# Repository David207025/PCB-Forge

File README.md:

# PCB Forge ⚡

A comprehensive, developer-centric documentation toolchain for hardware and PCB engineers. **PCB Forge** integrates a **VS Code extension**, a **native Rust backend (`pcbfapi`)**, automated **KiCad CLI** exports, and an in-memory **Typst** compilation engine to generate publication-grade PDF documentation, manufacturing packets, and schematic sheets directly from your EDA project files.

**Note:** The current repository status is for the new implementation of PCB-Forge. Past versions have been deleted due to incompatibility and performance issues.

---

## 🏗️ Architecture Overview

The PCB Forge monorepo is structured into three primary components:

```
PCB-Forge/
├── pcbfapi/                   # Native Rust background daemon & HTTP server
│   ├── src/
│   │   ├── main.rs            # Axum HTTP server (port 47210), CLI subcommands & system tray
│   │   ├── access.rs          # KiCad detection, TCC permission checking & access requests
│   │   ├── service.rs         # Background daemon manager (launchd, systemd, Windows service)
│   │   ├── forge.rs           # KiCad CLI runner, asset caching & Typst compiler
│   │   ├── definitions.rs     # Typst World implementation & project schema models
│   │   └── tray.rs            # Native macOS / Windows system tray icon & menu
│   └── typst/                 # Vendored Typst packages (e.g., cmarker plugin)
│
├── extension/                 # VS Code extension (TypeScript)
│   ├── src/extension.ts       # Extension entry point, daemon connector & webview provider
│   ├── web-ui/                # Modern React + Vite frontend for template & project editing
│   └── package.json           # Extension manifest & configuration
│
├── docs/                      # Auto-generated Markdown documentation (pcbfapi.md, scripts.md)
└── scripts                    # Workspace build, release, and packaging utilities
```

### How It Works
1. **The API Daemon (`pcbfapi`)**: A secure, persistent background daemon process written in Rust. It runs independently of VS Code, auto-starts on boot (via macOS LaunchAgent, Linux systemd, or Windows startup), and exposes local loopback endpoints on `http://127.0.0.1:47210`.
2. **KiCad Access & Permissions (`pcbfapi/src/access.rs`)**: Automatically checks for `kicad-cli`, resolves permissions, isolates configuration to prevent macOS TCC sandboxing issues, and prompts the user with native OS dialogs if access to KiCad application files is required.
3. **The Extension (`extension/`)**: Seamlessly connects to the background daemon over the HTTP endpoint. Shows daemon connection status in the VS Code status bar and provides commands to manage the service and verify permissions.
4. **Asset Generation & Typst Compilation**: Hardware schematics, layer SVGs, markdown notes, and project metadata are exported via KiCad CLI and compiled in-memory to publication-grade vector PDFs.

---

## ⚙️ Service & Daemon Management

The `pcbfapi` binary can be installed and managed as a background service:

```bash
# Verify KiCad installation and prompt for access if permissions are missing:
pcbfapi check-access

# Service management (auto-starts from boot):
pcbfapi service install    # Register background daemon (macOS LaunchAgent / systemd)
pcbfapi service start      # Start daemon service
pcbfapi service stop       # Stop daemon service
pcbfapi service status     # Inspect daemon & service status
pcbfapi service uninstall  # Remove background service registration
```

### Homebrew Installation & Services
When installing via Homebrew, `pcbfapi` is automatically configured as a background service:
```bash
brew tap David207025/homebrew-pcb-forge
brew install pcbfapi
brew services start pcbfapi
```

---

## 🛠️ Subscripts Tutorial & Reference

The project includes several automation scripts at the repository root. Below is a detailed guide on what each script does and when to use it:

### 1. `deploy-extension.js` — Local Extension Development
* **Command:** `pnpm deploy` or `node deploy-extension.js`
* **What it does:**
  1. Runs `pnpm build` (which compiles `extension/web-ui` with Vite and compiles extension TypeScript with `tsc`).
  2. Runs `node package-extension.js` to create the `.vsix` installer package.
  3. Automatically executes `code --install-extension <path-to-vsix> --force` to install the newly built extension directly into your local VS Code.
* **When to use:** Whenever you make changes to the VS Code extension or webview and want to test them immediately in VS Code.

### 2. `package-extension.js` — VSIX Package Bundler
* **Command:** `pnpm package` or `node package-extension.js`
* **What it does:**
  1. Copies the built webview bundle from `extension/web-ui/dist/` into `extension/web/`.
  2. Invokes `@vscode/vsce package` with clean exclusions (ignoring node_modules, source TS files, and web-ui source code) to produce a lean `.vsix` file in the `build/` directory.
* **When to use:** When you need a clean `.vsix` bundle for distribution without installing it locally.

### 3. `update-version.js` — Monorepo Version Synchronizer
* **Command:** `node update-version.js <new-version>` (e.g. `node update-version.js 0.4.0`)
* **What it does:**
  * Synchronizes the semantic version across all four project manifests in one pass:
    - Root `package.json`
    - Rust crate `pcbfapi/Cargo.toml` (`[package]` section)
    - Extension manifest `extension/package.json`
    - Frontend manifest `extension/web-ui/package.json`
* **When to use:** Before making a new release or when bumping version numbers.

### 4. `generate-docs.js` — Automated Markdown Documentation Generator
* **Command:** `pnpm docs` or `node generate-docs.js`
* **What it does:**
  1. Scans all Rust source files in `pcbfapi/src/` (`main.rs`, `forge.rs`, `definitions.rs`, `tray.rs`), extracting module-level documentation (`//!`) and item doc comments (`///`).
  2. Scans TypeScript and JavaScript scripts for JSDoc comment blocks (`/** ... */`).
  3. Writes comprehensive Markdown documentation files into the `docs/` folder:
     - `docs/pcbfapi.md`: Rust API handlers, endpoints, structs, and compiler world methods.
     - `docs/scripts.md`: Script functions and packaging documentation.
     - `docs/README.md`: Technical documentation index.
* **When to use:** Whenever you add or modify Rust functions, API endpoints, or scripts, or automatically as part of the release workflow.

### 5. `release.sh` — Unified End-to-End Release Pipeline
* **Command:** `./release.sh [new-version]` (e.g. `./release.sh 0.4.0` or `./release.sh`)
* **What it does:**
  1. Updates the version across all manifests if a version parameter is passed.
  2. Runs `node generate-docs.js` to update documentation in `docs/`.
  3. Builds frontend webview and compiles extension TypeScript (`pnpm run build`).
  4. Packages the `.vsix` extension bundle.
  5. Publishes the extension to the VS Code Marketplace if `VSCE_PAT` is defined.
  6. Commits modified files and pushes to `origin main`.
  7. Cleans up any existing GitHub release/tag for this version (using `gh release delete`).
  8. Creates and pushes a fresh Git tag (`vX.Y.Z`), triggering the GitHub Actions `cargo-dist` workflow to build cross-platform binaries, installers, and update the Homebrew tap.
* **When to use:** When you are ready to publish a new official release of PCB Forge.

### 6. `retag.sh` — CI Re-trigger & VSIX Publish Utility
* **Command:** `./retag.sh`
* **What it does:**
  * Reads the current version from `pcbfapi/Cargo.toml`.
  * Builds and packages the `.vsix` bundle and publishes it to the VS Code Marketplace via `@vscode/vsce`.
  * Deletes any existing GitHub Release and local/remote Git tag for that version, then recreates and pushes the tag to re-trigger CI.
* **When to use:** When you need to publish an updated VSIX and re-trigger CI builds for the current version without bumping the version number.

### 7. `wipe-tag.sh` — Tag Teardown Utility
* **Command:** `./wipe-tag.sh`
* **What it does:**
  * Extracts the current version from `pcbfapi/Cargo.toml` and permanently deletes the tag locally and on GitHub remote without recreating it.
* **When to use:** When canceling a release or removing an accidental tag.

### 8. `install-api.sh` — Local CLI Daemon Installation
* **Command:** `./install-api.sh`
* **What it does:**
  * Runs `cargo build --release` inside `pcbfapi/` and copies the compiled binary to `~/.pcb-forge/bin/pcbfapi`.
* **When to use:** When developing or testing the Rust daemon natively on your system.

### 9. `generate_icons.py` — Icon Generator
* **Command:** `python3 generate_icons.py`
* **What it does:**
  * Uses Pillow / Python to generate multi-resolution PNG and icon assets from the master icon files for the system tray and extension.

---

## 🚀 Quick Start for Development

### Prerequisites
- **Node.js** (v18+) & **pnpm**
- **Rust** & **Cargo** (latest stable)
- **KiCad 7+ or 8+** (with `kicad-cli` on PATH)
- **GitHub CLI (`gh`)** (optional, for release management)

### Local Build & Test Loop

1. **Install Dependencies:**
   ```bash
   pnpm install
   ```

2. **Check & Build Rust API Backend:**
   ```bash
   cargo check --manifest-path pcbfapi/Cargo.toml
   cargo build --manifest-path pcbfapi/Cargo.toml
   ```

3. **Develop the VS Code Extension & Webview:**
   ```bash
   # Build frontend and install extension into VS Code:
   pnpm deploy
   ```

4. **Generate Documentation:**
   ```bash
   pnpm docs
   ```

---

## 🧪 Example & Testing Environment

A complete, self-contained example workspace is available in the [`test/`](./test) directory (see [`test/README.md`](./test/README.md) for full setup and usage instructions). It includes a sample `.pcbf` project configuration, cloned **Venturi** KiCad schematic and PCB files, and an automated script that installs the required template into `~/.pcb-forge/templates`, syncs its schema, and compiles a full multi-page PDF document via the `pcbfapi` daemon.

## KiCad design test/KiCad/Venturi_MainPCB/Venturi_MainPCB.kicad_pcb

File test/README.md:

# PCB Forge — Example & Test Workspace

This directory contains a complete, ready-to-run example project (featuring a clone of the **Venturi** PCB hardware files) so you can test **PCB Forge** out of the box.

## Prerequisites

Before running this example, ensure the following are installed on your system:

1. **PCB Forge Daemon (`pcbfapi`)**: Must be installed and running on `127.0.0.1:47210`. See the [root README.md](../README.md) for Homebrew and binary installation instructions.
2. **KiCad (7.0, 8.0, or 9.0)**: `kicad-cli` must be installed and accessible (`pcbfapi check-access`).
3. **VS Code Extension** *(optional, for interactive editing)*: Install the **PCB Forge** extension in VS Code to edit `.pcbf` files with syntax highlighting, inline file pickers, and one-click PDF generation.

## What's Included

- **Sample `.pcbf` Project**: Pre-configured project definition linking schematic, PCB layout, and documentation pages using relative paths.
- **Venturi Hardware Assets**: Reference `.kicad_pcb` and `.kicad_sch` files used to test automated SVG layer exports.
- **Template & Setup Script**: Copies the required document template into `~/.pcb-forge/templates/src/`, generates its JSON schema, and compiles the example PDF via the `pcbfapi` daemon.

## Running the Example

From inside the `test/` directory, run the included setup and generation script:

```bash
chmod +x run-test.sh   # if not already executable
./run-test.sh
```

Once complete, the compiled multi-page PDF is written directly into this folder alongside the .pcbf project file. You can also open the .pcbf file in VS Code and run PCB Forge: Generate Project from the Command Palette (Cmd+Shift+P / Ctrl+Shift+P).

---

### 4. Root `README.md` Updates

Add the **VS Code Extension Installation** section under **Service & Daemon Management**, update the `retag.sh` entry, and expand the **Testing & Examples** section at the bottom:

```markdown
### VS Code Extension Installation

You can install the **PCB Forge** extension in either of two ways:

1. **From the VS Code Marketplace (Recommended):**
   - Open VS Code, go to the **Extensions** view (`Cmd+Shift+X` / `Ctrl+Shift+X`), search for **PCB Forge**, and click **Install**.
   - Or install via CLI:
     ```bash
     code --install-extension David207025.pcb-forge
     ```

2. **From a `.vsix` Release Package (or for VS Code Forks such as Antigravity):**
   - Download `pcb-forge-<version>.vsix` from the [GitHub Releases](../../releases) page (or build it locally with `./build-vsix.sh`).
   - In VS Code / Antigravity, open **Extensions** -> `...` (More Actions) -> **Install from VSIX...** and select the downloaded file, or install from the terminal:
     ```bash
     code --install-extension build/pcb-forge-<version>.vsix --force
     # Or for Antigravity IDE:
     agy-ide --install-extension build/pcb-forge-<version>.vsix --force
     ```

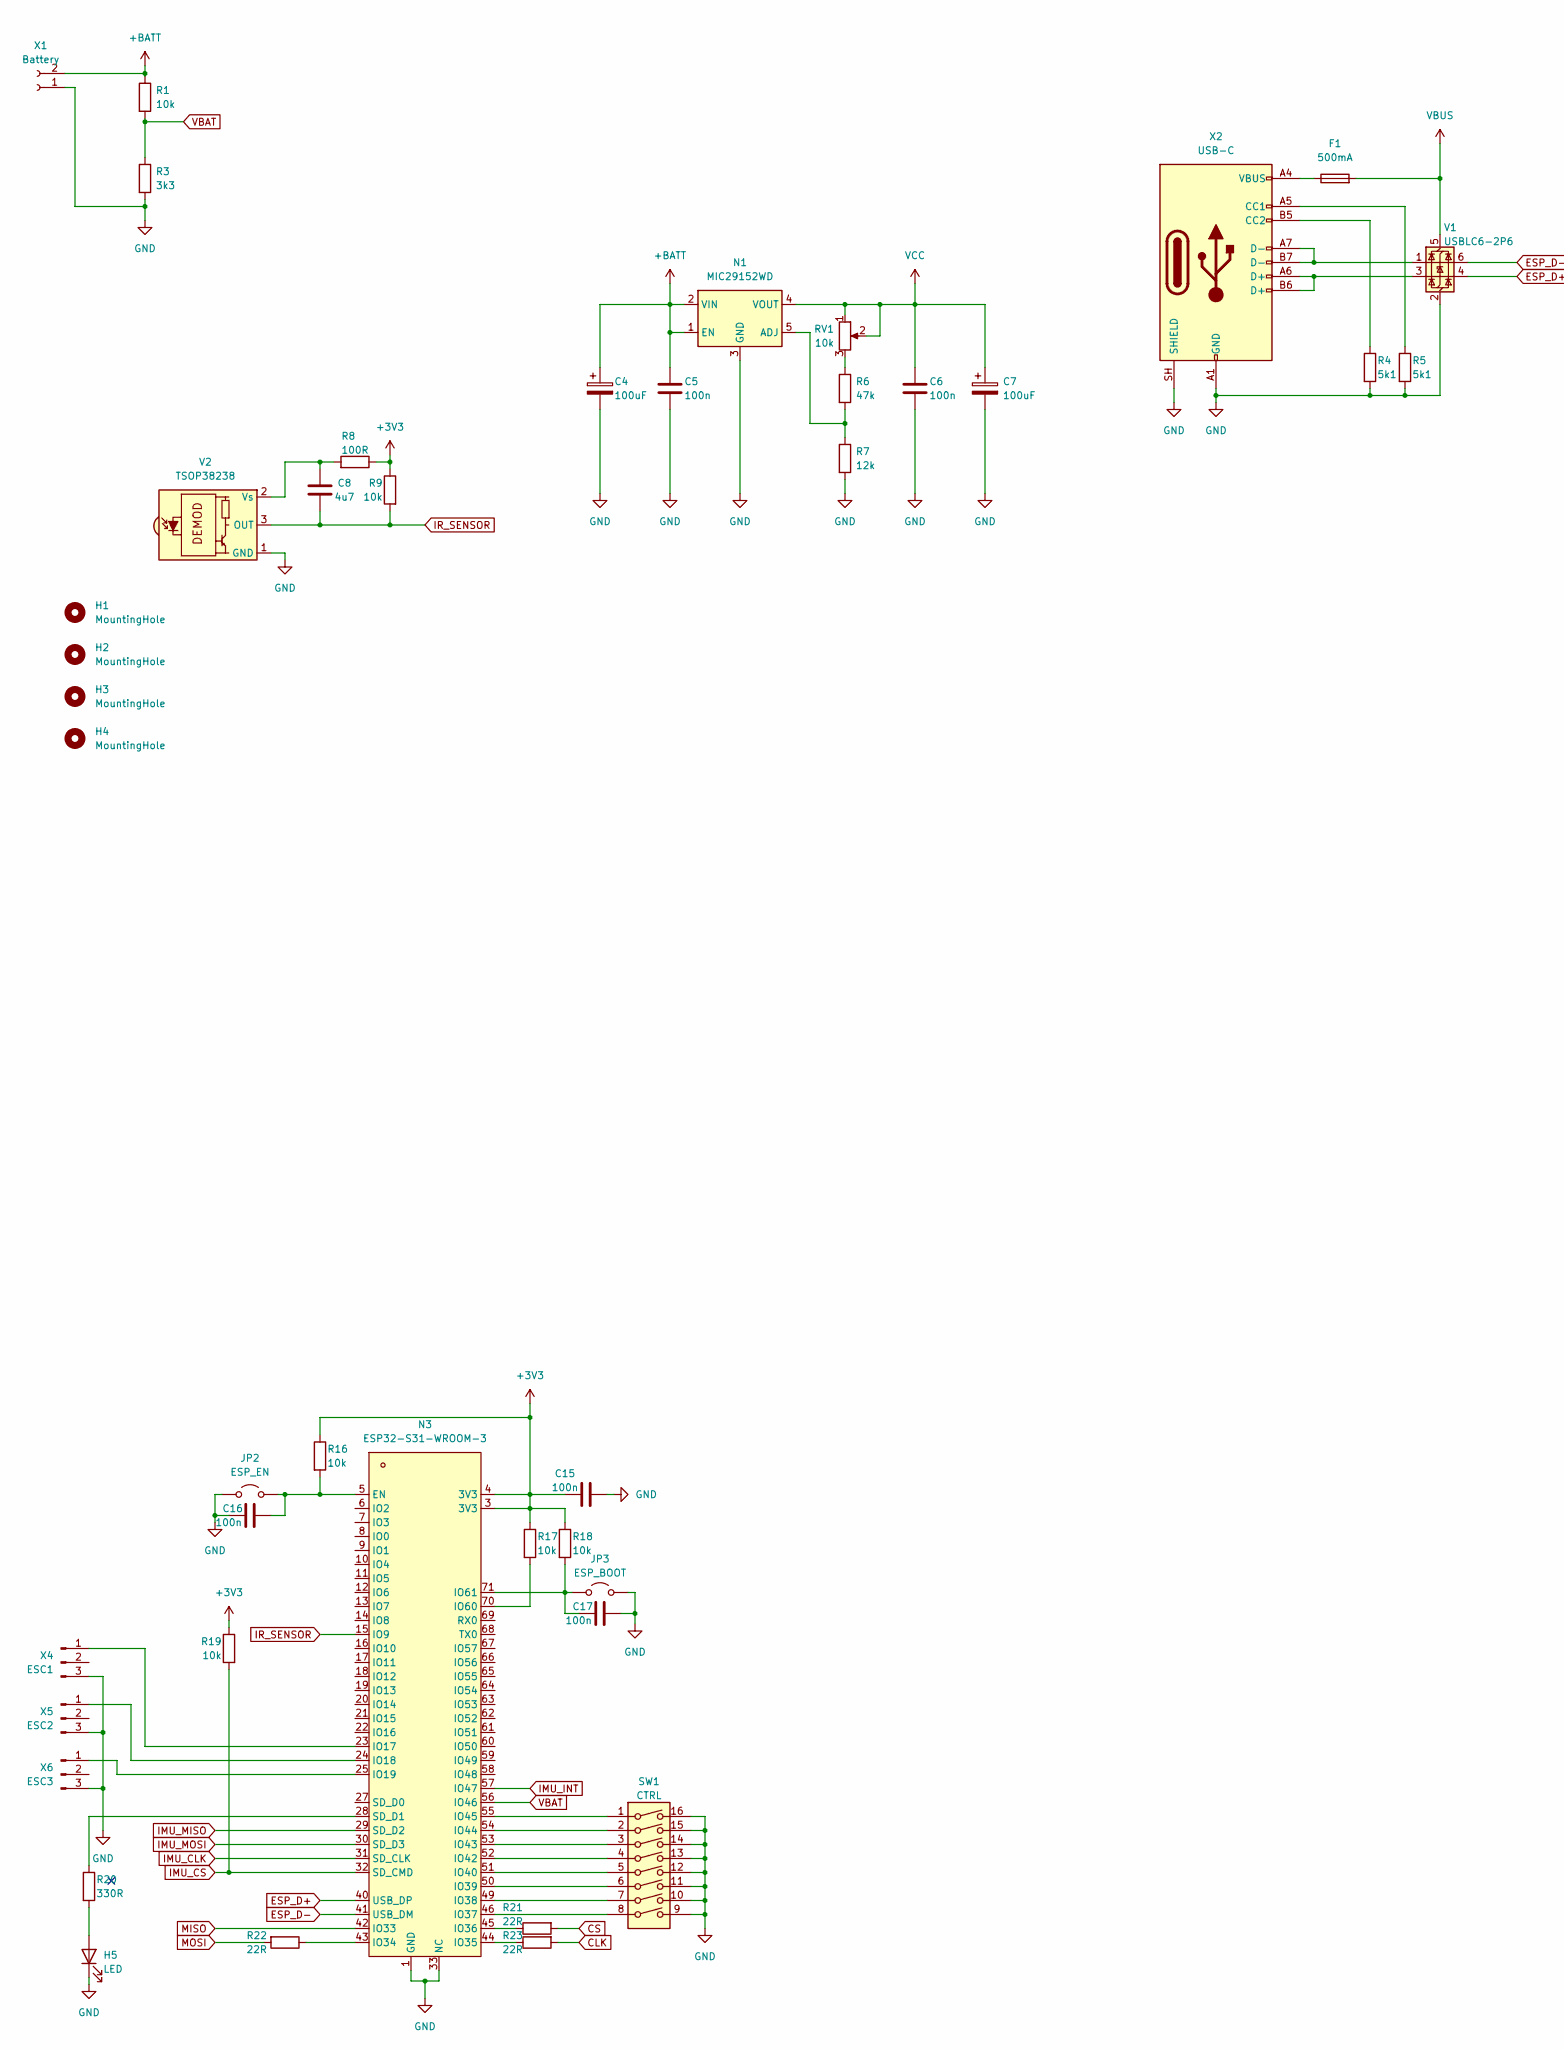
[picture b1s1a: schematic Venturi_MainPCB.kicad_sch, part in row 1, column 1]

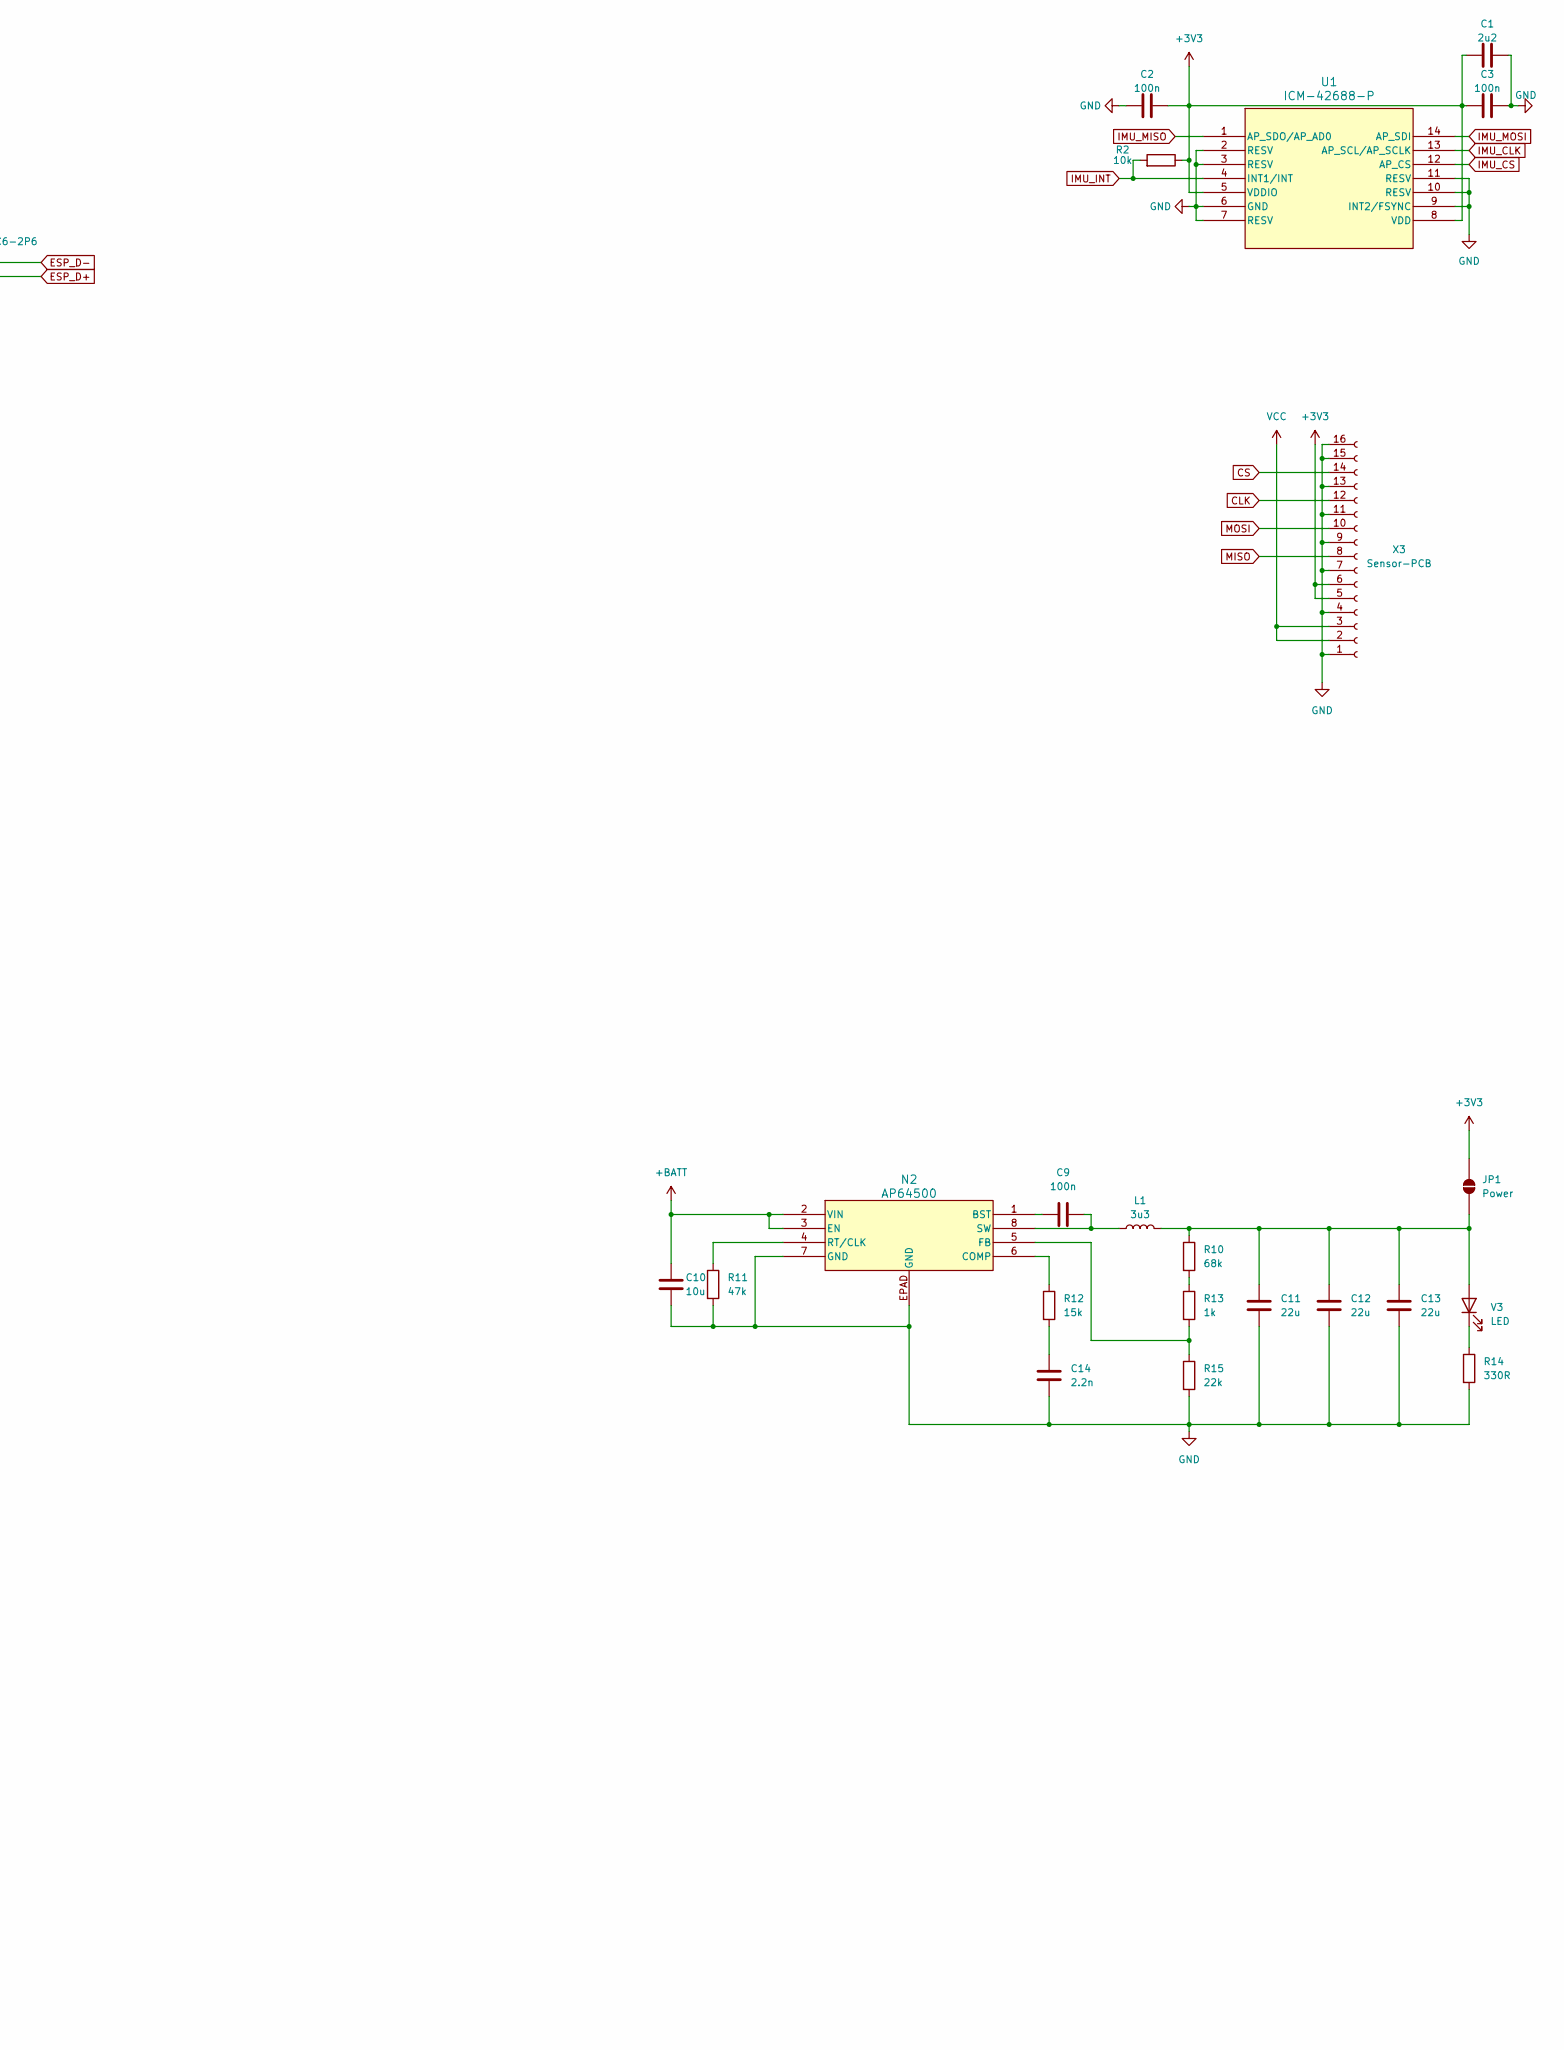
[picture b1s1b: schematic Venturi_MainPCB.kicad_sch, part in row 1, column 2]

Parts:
C1: 2u2; C_0805_2012Metric_Pad1.18x1.45mm_HandSolder
C2, C3, C5, C6, C15, C16, C17: 100n; C_0805_2012Metric_Pad1.18x1.45mm_HandSolder
C4, C7: 100uF; CP_EIA-7343-15_Kemet-W_HandSolder
C8: 4u7; C_0805_2012Metric_Pad1.18x1.45mm_HandSolder
C9: 100n; C_0603_1608Metric_Pad1.08x0.95mm_HandSolder
C10: 10u; C_0603_1608Metric_Pad1.08x0.95mm_HandSolder
C11, C12, C13: 22u; C_0603_1608Metric_Pad1.08x0.95mm_HandSolder
C14: 2.2n; C_0603_1608Metric_Pad1.08x0.95mm_HandSolder
F1: 500mA; Fuse_0805_2012Metric_Pad1.15x1.40mm_HandSolder
H1, H2, H3, H4: MountingHole; MountingHole_3.2mm_M3
H5: LED; LED_0805_2012Metric_Pad1.15x1.40mm_HandSolder
JP1: Power; SolderJumper-2_P1.3mm_Open_TrianglePad1.0x1.5mm
JP2: ESP_EN; TestPoint_2Pads_Pitch2.54mm_Drill0.8mm
JP3: ESP_BOOT; TestPoint_2Pads_Pitch2.54mm_Drill0.8mm
L1: 3u3; L_1008_2520Metric
N1: MIC29152WD; TO-252-5_TabPin3
N2: AP64500; SO-8EP_DIO
N3: ESP32-S31-WROOM-3; MPN ESP32-S31-WROOM-3; LCSC Part C9900281993
R1, R2, R9, R16, R17, R18, R19: 10k; R_0805_2012Metric_Pad1.20x1.40mm_HandSolder
R3: 3k3; R_0805_2012Metric_Pad1.20x1.40mm_HandSolder
R4, R5: 5k1; R_0805_2012Metric_Pad1.20x1.40mm_HandSolder
R6: 47k; R_0805_2012Metric_Pad1.20x1.40mm_HandSolder
R7: 12k; R_0805_2012Metric_Pad1.20x1.40mm_HandSolder
R8: 100R; R_0805_2012Metric_Pad1.20x1.40mm_HandSolder
R10: 68k; R_0603_1608Metric_Pad0.98x0.95mm_HandSolder
R11: 47k; R_0603_1608Metric_Pad0.98x0.95mm_HandSolder
R12: 15k; R_0603_1608Metric_Pad0.98x0.95mm_HandSolder
R13: 1k; R_0603_1608Metric_Pad0.98x0.95mm_HandSolder
R14: 330R; R_0603_1608Metric_Pad0.98x0.95mm_HandSolder
R15: 22k; R_0603_1608Metric_Pad0.98x0.95mm_HandSolder
R20: 330R; R_0805_2012Metric_Pad1.20x1.40mm_HandSolder
R21, R22, R23: 22R; R_0805_2012Metric_Pad1.20x1.40mm_HandSolder
RV1: 10k; Potentiometer_Bourns_3314J_Vertical
SW1: CTRL; SW_DIP_SPSTx08_Slide_KingTek_DSHP08TJ_W5.25mm_P1.27mm_JPin
U1: ICM-42688-P; LGA-14_3x2.5mm_P0.5mm_LayoutBorder3x4y
V1: USBLC6-2P6; SOT-666
V2: TSOP38238; Vishay_MINICAST-3Pin
V3: LED; LED_0805_2012Metric_Pad1.15x1.40mm_HandSolder
X1: Battery; AMASS_XT30U-M_1x02_P5.0mm_Vertical
X2: USB-C; USB_C_Receptacle_G-Switch_GT-USB-7010ASV
X3: Sensor-PCB; SensorPCB-Connector
X4: ESC1; PinHeader_1x03_P2.54mm_Vertical
X5: ESC2; PinHeader_1x03_P2.54mm_Vertical
X6: ESC3; PinHeader_1x03_P2.54mm_Vertical

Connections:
+3V3: C1.2, C2.1, C3.2, C15.1, JP1.2 (B), N3.3 (3V3), N3.4 (3V3), R2.1, R8.1, R9.1, R16.1, R17.1, R18.1, R19.1, U1.5 (VDDIO), U1.8 (VDD), X3.5, X3.6
+BATT: C4.1, C5.1, C10.2, N1.1 (EN), N1.2 (VIN), N2.2 (VIN), N2.3 (EN), R1.1, X1.2
CLK: R23.2, X3.12
CS: R21.2, X3.14
ESP_D+: N3.40 (USB_DP), V1.4 (I/O2)
ESP_D-: N3.41 (USB_DM), V1.6 (I/O1)
GND: C1.1, C2.2, C3.1, C4.2, C5.2, C6.2, C7.2, C10.1, C11.1, C12.1, C13.1, C14.2, C15.2, C16.1, C17.2, H5.1 (K), JP2.1 (A), JP3.2 (B), N1.3 (GND), N2.7 (GND), N2.EPAD (GND), N3.1 (GND), N3.2 (GND), N3.26 (GND), N3.33 (NC), N3.34 (NC), N3.35 (NC), N3.36 (NC), N3.37 (NC), N3.38 (NC), N3.39 (NC), N3.47 (GND), N3.48 (GND), N3.72 (GND), N3.73 (GND), N3.74 (GND), N3.75 (GND), N3.76 (GND), N3.77 (GND), N3.78 (GND), N3.79 (GND), N3.80 (GND), N3.81 (GND), N3.82 (GND), N3.83 (GND), N3.84 (GND), N3.85 (GND), N3.86 (GND), N3.87 (GND), N3.88 (GND), N3.89 (GND), N3.90 (GND), N3.91 (NC), N3.92 (GND), N3.93 (GND), N3.94 (GND), N3.95 (GND), N3.96 (GND), N3.97 (GND), N3.98 (GND), N3.99 (GND), R3.2, R4.2, R5.2, R7.2, R11.2, R14.2, R15.2, SW1.9, SW1.10, SW1.11, SW1.12, SW1.13, SW1.14, SW1.15, SW1.16, U1.2 (RESV), U1.3 (RESV), U1.6 (GND), U1.7 (RESV), U1.9 (INT2/FSYNC), U1.10 (RESV), U1.11 (RESV), V1.2 (GND), V2.1 (GND), X1.1, X2.A1 (GND), X2.A12 (GND), X2.B1 (GND), X2.B12 (GND), X2.SH (SHIELD), X3.1, X3.4, X3.7, X3.9, X3.11, X3.13, X3.15, X3.16, X4.3, X5.3, X6.3
IMU_CLK: N3.31 (SD_CLK), U1.13 (AP_SCL/AP_SCLK)
IMU_CS: N3.32 (SD_CMD), R19.2, U1.12 (AP_CS)
IMU_INT: N3.57 (IO47), R2.2, U1.4 (INT1/INT)
IMU_MISO: N3.29 (SD_D2), U1.1 (AP_SDO/AP_AD0)
IMU_MOSI: N3.30 (SD_D3), U1.14 (AP_SDI)
IR_SENSOR: C8.1, N3.15 (IO9), R9.2, V2.3 (OUT)
MISO: N3.42 (IO33), X3.8
MOSI: R22.2, X3.10
unnamed: C14.1, R12.2
unnamed: F1.1, X2.A4 (VBUS), X2.A9 (VBUS), X2.B4 (VBUS), X2.B9 (VBUS)
unnamed: H5.2 (A), R20.2
unnamed: C11.2, C12.2, C13.2, JP1.1 (A), L1.2, R10.1, V3.2 (A)
unnamed: C16.2, JP2.2 (B), N3.5 (EN), R16.2
unnamed: C17.1, JP3.1 (A), N3.71 (IO61), R18.2
unnamed: N1.5 (ADJ), R6.2, R7.1
unnamed: C9.1, N2.1 (BST)
unnamed: N2.6 (COMP), R12.1
unnamed: N2.5 (FB), R13.2, R15.1
unnamed: N2.4 (RT/CLK), R11.1
unnamed: C9.2, L1.1, N2.8 (SW)
unnamed: N3.23 (IO17), X4.1
unnamed: N3.24 (IO18), X5.1
unnamed: N3.25 (IO19), X6.1
unnamed: N3.43 (IO34), R22.1
unnamed: N3.44 (IO35), R23.1
unnamed: N3.45 (IO36), R21.1
unnamed: N3.46 (IO37), SW1.8
unnamed: N3.49 (IO38), SW1.7
unnamed: N3.50 (IO39), SW1.6
unnamed: N3.51 (IO40), SW1.5
unnamed: N3.52 (IO42), SW1.4
unnamed: N3.53 (IO43), SW1.3
unnamed: N3.54 (IO44), SW1.2
unnamed: N3.55 (IO45), SW1.1
unnamed: N3.70 (IO60), R17.2
unnamed: N3.28 (SD_D1), R20.1
unnamed: R6.1, RV1.3
unnamed: R10.2, R13.1
unnamed: V1.1 (I/O1), X2.A7 (D-), X2.B7 (D-)
unnamed: V1.3 (I/O2), X2.A6 (D+), X2.B6 (D+)
unnamed: C8.2, R8.2, V2.2 (Vs)
unnamed: R14.1, V3.1 (K)
unnamed: R5.1, X2.A5 (CC1)
unnamed: R4.1, X2.B5 (CC2)
VBAT: N3.56 (IO46), R1.2, R3.1
VBUS: F1.2, V1.5 (VBUS)
VCC: C6.1, C7.1, N1.4 (VOUT), RV1.1, RV1.2, X3.2, X3.3

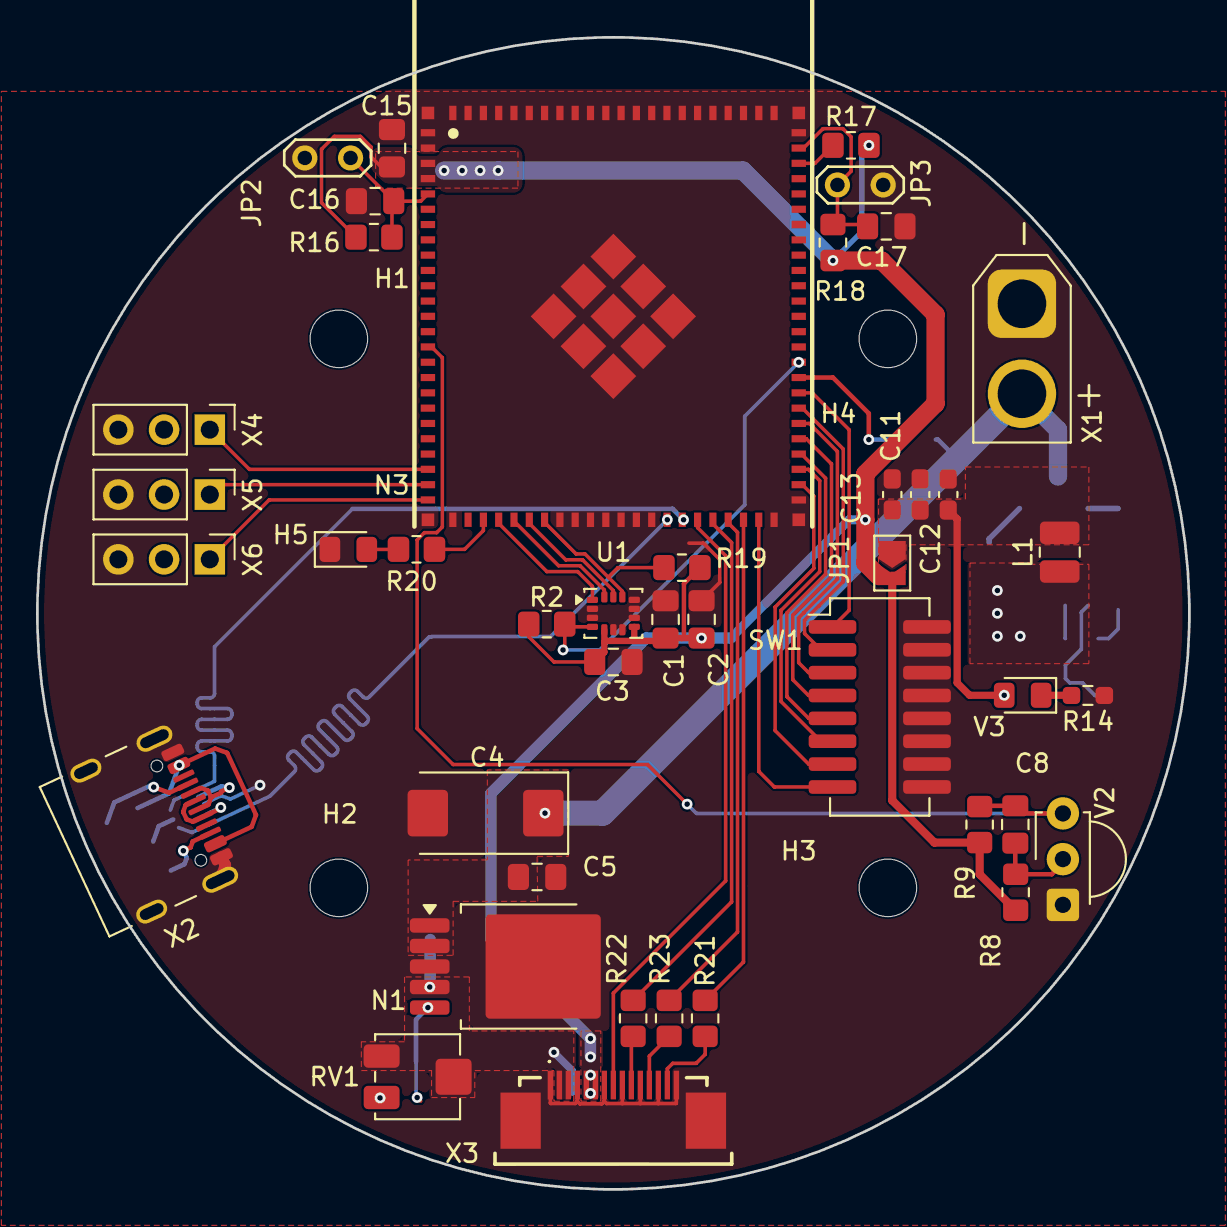
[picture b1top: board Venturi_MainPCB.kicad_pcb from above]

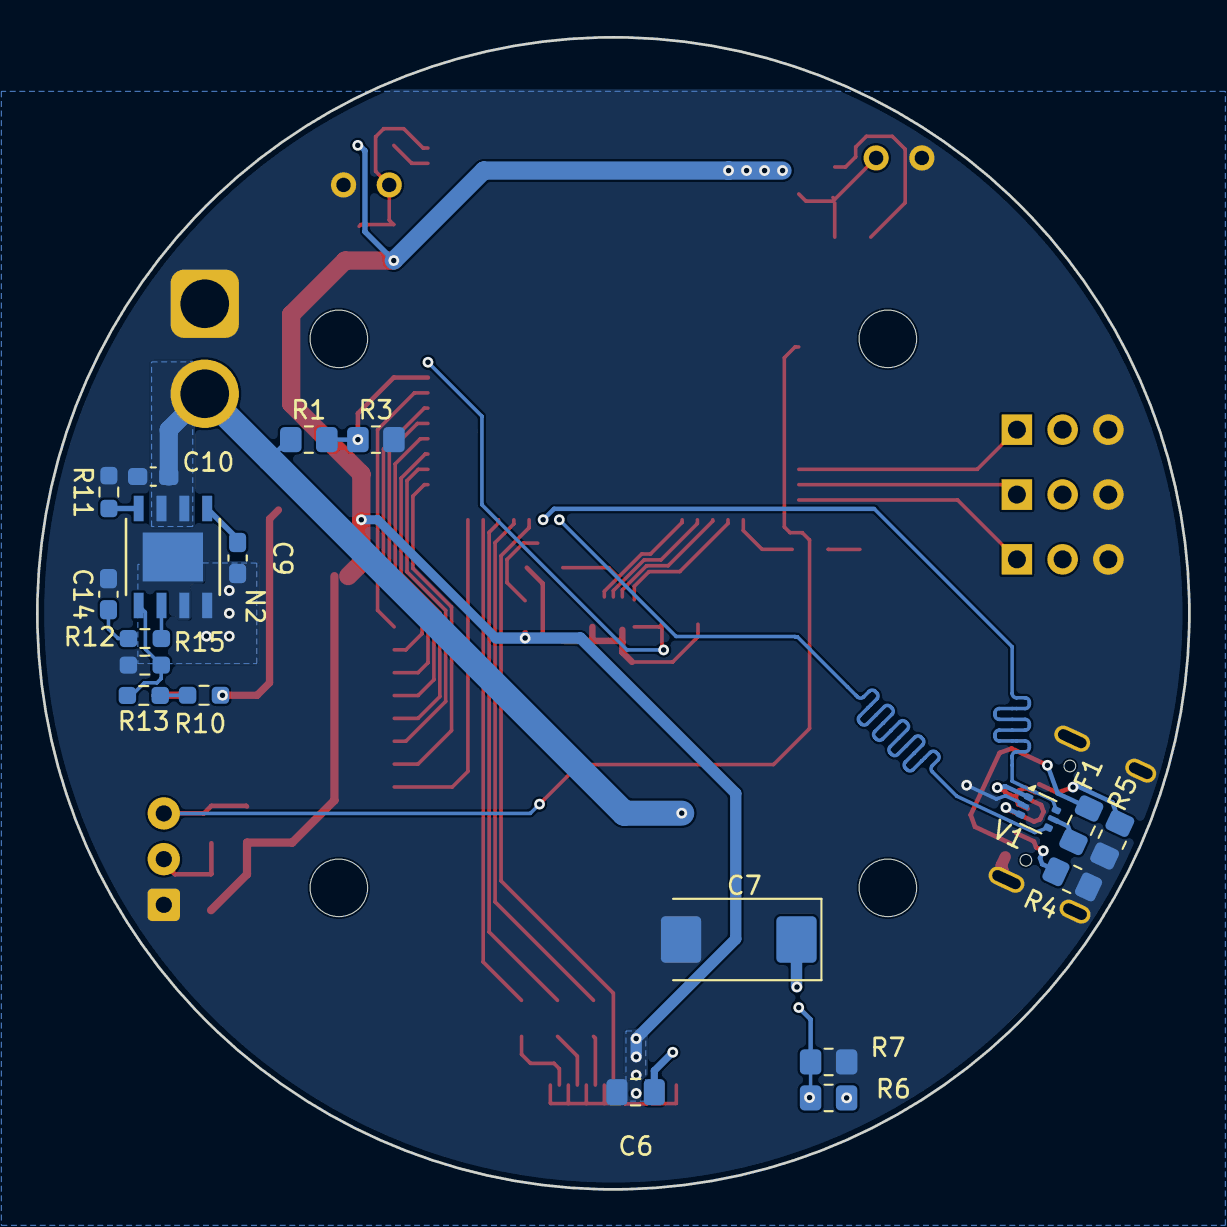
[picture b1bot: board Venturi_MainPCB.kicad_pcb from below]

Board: 4 copper layers, 64.0 x 64.0 mm, 65 parts (19 on the bottom side), 54 nets.

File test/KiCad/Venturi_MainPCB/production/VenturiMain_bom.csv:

Designator,Footprint,Quantity,Value,LCSC Part #
C1,0805,1,2u2,
C10,0603,1,10u,
"C11, C12, C13",0603,3,22u,
C14,0603,1,2.2n,
"C15, C16, C17, C2, C3, C5, C6",0805,7,100n,
"C4, C7",CP_EIA-7343-15_Kemet-W_HandSolder,2,100uF,
C8,0805,1,4u7,
C9,0603,1,100n,
F1,0805,1,500mA,
"H5, V3",0805,2,LED,
JP2,TestPoint_2Pads_Pitch2.54mm_Drill0.8mm,1,ESP_EN,
JP3,TestPoint_2Pads_Pitch2.54mm_Drill0.8mm,1,ESP_BOOT,
L1,1008,1,3u3,
N1,TO-252-5_TabPin3,1,MIC29152WU,
N2,SO-8EP_DIO,1,AP64500,
N3,ESP32-S31-WROOM-3,1,ESP32-S31-WROOM-3,C9900281993
"R1, R16, R17, R18, R19, R2, R9",0805,7,10k,
R10,0603,1,68k,
R11,0603,1,47k,
R12,0603,1,15k,
R13,0603,1,1k,
R14,0603,1,330R,
R15,0603,1,22k,
R20,0805,1,330R,
"R21, R22, R23",0805,3,22R,
R3,0805,1,3k3,
"R4, R5",0805,2,5k1,
R6,0805,1,47k,
R7,0805,1,12k,
R8,0805,1,100R,
RV1,Potentiometer_Bourns_3314J_Vertical,1,10k,
SW1,SW_DIP_SPSTx08_Slide_KingTek_DSHP08TJ_W5.25mm_P1.27mm_JPin,1,CTRL,
U1,LGA-14_3x2.5mm_P0.5mm_LayoutBorder3x4y,1,ICM-42688-P,
V1,SOT-666,1,USBLC6-2P6,
V2,Vishay_MINICAST-3Pin,1,TSOP38238,
X1,AMASS_XT30U-M_1x02_P5.0mm_Vertical,1,Battery,
X2,USB_C_Receptacle_G-Switch_GT-USB-7010ASV,1,USB-C,
X3,SensorPCB-Connector,1,Sensor-PCB,
X4,PinHeader_1x03_P2.54mm_Vertical,1,ESC1,
X5,PinHeader_1x03_P2.54mm_Vertical,1,ESC2,
X6,PinHeader_1x03_P2.54mm_Vertical,1,ESC3,
